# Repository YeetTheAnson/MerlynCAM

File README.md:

# MerlynCAM

https://github.com/user-attachments/assets/a9457055-48cb-43b0-b4a9-4c273cf0078e

https://github.com/user-attachments/assets/13ca98ed-bc15-4bd0-ae74-1581ccfe5670

## Introduction
This project was made possible thanks the reverse engineering efforts done by the OpenIPC team! You can check out their supported hardware here: https://openipc.org/supported-hardware/featured and the reference project here: https://oshwlab.com/oshwhub.com/openipc-vtx-ssc338q-30kq

This is my custom action camera, the MerlynCAM! This project was made to record HD footage on my FPV drones. It records video at 1080p@90, 1440p@60 and 4k@20. It also includes a BMI270 gyro to log motion data at 150Hz for Gyroflow video stabilization, and an ICS-43434 I2S microphone to capture propeller noise for the viewer's immersion.

The MerlynCAM is powered by the Sigmastar SSC338Q SOC. It is easy to use and includes a low power microcontroller onboard to manage the LED indicators, buttons, and power saving modes. There is only one button used for powering the camera on and off and starting and stopping recordings. The microcontroller handles the rest of the quality of life features in the background, such as battery level monitoring and auto power on when external voltage is detected in FPV mode. It also has an internal 1S battery with a BQ25606 charging circuit, so it can be used like a normal action cam or with the batteries removed to save weight on a drone.

## User Guide
The MerlynCAM is operated using a single button and it shows charge status and battery levels using a White LED

### Power & Recording Control
- **Power On:** Press the button once, then press and hold for 2 seconds. The White LED will blink rapidly while holding, then turn solid to indicate it is booting. Release the button afterwards.

> [!TIP]
> The camera will refuse to power on if the battery is below 5%

- **Power Off:** Press and hold the button for 4 seconds. The White LED will blink rapidly after 2 seconds, then blink twice and turn off.

- **Start/Stop Recording:** While the camera is powered on, hold the button for 1 second to start recording. Hold for 1 second again to stop recording.

### Battery Level Checking
While powered off, press the button once. The White LED will blink to indicate the current charge level:

- **\>95%:** 4 normal blinks + 3 rapid blinks

- **80-95%** 4 blinks

- **60-79%:** 3 blinks

- **40-59%:** 2 blinks

- **20-39%:** 1 blink

- **\< 5%:** 3 rapid blinks

### Passive Indicator
- **Charging:** The white LED will pulse slowly while charging. Once fully charged, it will remain solid until the power is disconnected

- **Battery Status:** The White LED automatically flashes the current battery percentage every 3.5 seconds

> [!IMPORTANT]
> Bridge the CHRG pad on the PCB if no battery is connected. This is necessary for the battery management IC to output a stable voltage on external power.

## Hardware Specifications
* **SOC:** Sigmastar SSC338Q
* **Camera Interface:** 30 pin mezzanine connector (compatible with Orange Pi 5)
* **IMU:** BMI270 @ I2C
* **Microphone:** ICS-43434 @ I2S
* **Storage:** Micro SD Card slot + W25Q128JVSIQ 16MB NOR Flash
* **Power Management & User Interface:** CH32V003F4U6
* **Battery Management:** BQ25606
* **Power Supply:** TPS63802 buck boost (3.3V), RT8097CHGE buck (1.0V and 1.5V), RT9193-18GB LDO (1.8V)

## Hardware Overview

> [!WARNING]
> When ordering from JLCPCB, make sure to enable impedance control and use the JLC04161H-3313 Stackup 

## Firmware
Because the SSC338Q is a proprietary chip, it must run the OpenIPC linux environment. Building the firmware requires a linux filesystem (Windows isn't supported)

> [!WARNING]
> At least 20GB of free space is required to build OpenIPC

### How to build the firmware (SSC338Q)
1. Clone the OpenIPC [firmware repository](https://github.com/openipc/firmware)
2. Run `make` and select the infinity6e architecture on the TUI.
3. Navigate to `output/build/linux-custom/arch/arm/boot/dts/` and replace `infinity6e-ssc012b-s01a.dts` with [infinity6e-ssc012b-s01a.dts](https://github.com/YeetTheAnson/MerlynCAM/blob/main/firmware/source/openIPC/infinity6e-ssc012b-s01a.dts).
4. Run `make linux-rebuild` to update the custom DTS changes into the kernel.
5. Navigate to `output/build/images` and extract `openipc.ssc338q-nand-ultimate.tgz` by entering `tar -xzf openipc.ssc338q-nand-ultimate.tgz`
6. Navigate to ssc338q-nand-ultimate and enter the command in your terminal
 `dd if=uImage.ssc338q of=openipc-ssc338q-nor-ultimate-16mb.bin bs=1K seek=384 conv=notrunc` and the binary file should appear

### How to build the firmware (CH32V003)
1. Clone [this repository](https://github.com/YeetTheAnson/MerlynCAM/tree/main) and enter the directory `cd MerlynCAM`
2. Open the `/firmware/source/powerManagement/powerManagement.ino` file in ArduinoIDE
3. Paste `https://alexandermandera.github.io/arduino-wch32v003/package_ch32v003_index.json` into File > Preferences > Additional boards manager URLs
4. Go to boards manager and install `WCH Boards` by Alexander Mandera
5. Click the upload button or Sketch > Export Compiled Binary

### How to flash the firmware (SSC338Q)
The W25Q128 16MB flash chip comes blank from the factory and the openIPC bootloader must be flashed before the operating system is able to boot.
1. Connect the CH341A USB programmer or a [makeshift Arduino programmer](https://controllerstech.com/arduino-w25q-flash-memory/) to flash the binary file to the W25Q128 flash chip. The file can be obtained in [firmware/binaries/(SSC338Q)openipc-nor-ultimate-16mb.bin](https://github.com/YeetTheAnson/MerlynCAM/blob/main/firmware/binaries/(SSC338Q)openipc-nor-ultimate-16mb.bin) or the [OpenIPC repository](https://openipc.org/cameras/vendors/sigmastar/socs/ssc338q/download_full_image?flash_size=16&flash_type=nor&fw_release=ultimate&layout=16) or compiled locally.

### How to flash the firmware (CH32V003)
1. Connect the WCH Link USB adapter to the SWDIO test point

2. Connect the USB C port. The MerlynCAM PCB and WCH Link USB adapter must share common ground (e.g. connected to the same laptop)
3. If compiling locally, press the upload button in Arduino IDE. Or use WCH-LinkUtility if flashing the pre compile binary in [powerManagement.bin](https://github.com/YeetTheAnson/MerlynCAM/blob/main/firmware/binaries/%28CH32V003%29powerManagement.bin)

## Assembly

### Component List
* **Shell:**
    - [case.stl](https://github.com/YeetTheAnson/MerlynCAM/blob/main/production/3dPrint/case.stl)
    - [lid.stl](https://github.com/YeetTheAnson/MerlynCAM/blob/main/production/3dPrint/lid.stl)
    - [button.stl](https://github.com/YeetTheAnson/MerlynCAM/blob/main/production/3dPrint/button.stl)
* **PCB:**
    - [MerlynCAM.zip](https://github.com/YeetTheAnson/MerlynCAM/blob/main/production/PCB/MerlynCAM.zip)
* **Camera:** IMX415 camera module for Orange Pi 5 + 30P MIPI cable
* **Fasteners:**
    - 8x M2 6mm Self Tapping Screws
    - 4x M2 4mm Self Tapping Screws
* **Battery:** Generic 500mAh LiPo battery
* **SD Card:** Generic micro SD Card

### Assembly Instructions

1. Place IMX415 camera module in the case and secure with 4x 6mm Self Tapping Screws.

2. Insert button with the hole side facing up.

3. Solder the battery wires to designated pads and place the battery and PCB into the case. Route the MIPI cable through the recess of the case wall and connect to the mezzanine connector.

4. Secure the PCB to the case with 4x 6mm Self Tapping Screws.

5. Put on the case lid and secure with 4x 4mm Self Tapping Screws.

## Bill of Material
Note: The prices in USD are converted as of 1 September 2026 and may fluctuate. The costs of separate components are cheaper than JLCPCB assembly.

| Category | Item Name | Description | Link | Vendor | Quantity | Total Price (USD) |
|---|---|---|---|---|---:|---:|
| PCB Components | CL10A106MA8NRNC | 10uF 0603 capacitor | [link](https://www.lcsc.com/product-detail/C96446.html) | LCSC | 20 | 1.30 |
| PCB Components | CL05A475MP5NRNC | 4.7uF 0402 capacitor | [link](https://www.lcsc.com/product-detail/C23733.html) | LCSC | 50 | 1.17 |
| PCB Components | CL05B104KB54PNC | 0.1uF 0402 capacitor | [link](https://www.lcsc.com/product-detail/C307331.html) | LCSC | 100 | 0.89 |
| PCB Components | CC0402KRX7R9BB473 | 47nF 0402 capacitor | [link](https://www.lcsc.com/product-detail/C272875.html) | LCSC | 100 | 0.41 |
| PCB Components | CL05A105KA5NQNC | 1uF 0402 capacitor | [link](https://www.lcsc.com/product-detail/C52923.html) | LCSC | 50 | 0.61 |
| PCB Components | CL10A226MQ8NRNC | 22uF 0603 capacitor | [link](https://www.lcsc.com/product-detail/C59461.html) | LCSC | 20 | 0.63 |
| PCB Components | 0402B223K500NT | 22nF 0402 capacitor | [link](https://www.lcsc.com/product-detail/C1532.html) | LCSC | 50 | 0.58 |
| PCB Components | 0402CG8R0C500NT | 8pF 0402 capacitor | [link](https://www.lcsc.com/product-detail/C1578.html) | LCSC | 100 | 0.36 |
| PCB Components | CDZVT2R5.1B | 5.1V Clamp SOD923 zener | [link](https://www.lcsc.com/product-detail/C414245.html) | LCSC | 20 | 0.64 |
| PCB Components | HC-1.0-4PWT | 4P JST-SH connector | [link](https://www.lcsc.com/product-detail/C2845363.html) | LCSC | 5 | 0.47 |
| PCB Components | FTC201610S1R5MBCA | 1.5uH 0806 inductor | [link](https://www.lcsc.com/product-detail/C5832343.html) | LCSC | 10 | 0.98 |
| PCB Components | FTC201610SR47MBCA | 0.47 uH 0806 inductor | [link](https://www.lcsc.com/product-detail/C5832340.html) | LCSC | 10 | 0.98 |
| PCB Components | YLED0602RSIDE | Red 0602 right angle LED | [link](https://www.lcsc.com/product-detail/C49446796.html) | LCSC | 20 | 0.49 |
| PCB Components | YLED0602WSIDE | White 0602 right angle LED | [link](https://www.lcsc.com/product-detail/C46635136.html) | LCSC | 50 | 0.99 |
| PCB Components | AO3401A | P channel MOSFET | [link](https://www.lcsc.com/product-detail/C15127.html) | LCSC | 5 | 0.49 |
| PCB Components | 0402WGF1003TCE | 100k 0402 resistor | [link](https://www.lcsc.com/product-detail/C25741.html) | LCSC | 100 | 0.28 |
| PCB Components | FRC0402F2700TS | 270R 0402 resistor | [link](https://www.lcsc.com/product-detail/C2909342.html) | LCSC | 100 | 0.25 |
| PCB Components | FRC0402F9100TS | 910R 0402 resistor | [link](https://www.lcsc.com/product-detail/C2909392.html) | LCSC | 100 | 0.18 |
| PCB Components | 0402WGF1002TCE | 10k 0402 resistor | [link](https://www.lcsc.com/product-detail/C25744.html) | LCSC | 100 | 0.31 |
| PCB Components | 0402WGF5101TCE | 5.1k 0402 resistor | [link](https://www.lcsc.com/product-detail/C25905.html) | LCSC | 100 | 0.26 |
| PCB Components | 0402WGF5602TCE | 56k 0402 resistor | [link](https://www.lcsc.com/product-detail/C25796.html) | LCSC | 100 | 0.68 |
| PCB Components | 0402WGF1502TCE | 15k 0402 resistor | [link](https://www.lcsc.com/product-detail/C25756.html) | LCSC | 100 | 0.58 |
| PCB Components | FRC0402F3602TS | 36k 0402 resistor | [link](https://www.lcsc.com/product-detail/C2930004.html) | LCSC | 100 | 0.19 |
| PCB Components | 0402WGF1000TCE | 100R 0402 resistor | [link](https://www.lcsc.com/product-detail/C25076.html) | LCSC | 100 | 0.77 |
| PCB Components | 0402WGF5102TCE | 51k 0402 resistor | [link](https://www.lcsc.com/product-detail/C25794.html) | LCSC | 100 | 0.19 |
| PCB Components | 0402WGF4701TCE | 4.7k 0402 resistor | [link](https://www.lcsc.com/product-detail/C25900.html) | LCSC | 100 | 0.29 |
| PCB Components | 0402WGF2003TCE | 200k 0402 resistor | [link](https://www.lcsc.com/product-detail/C25764.html) | LCSC | 100 | 0.32 |
| PCB Components | TS24CA | Right angle button | [link](https://www.lcsc.com/product-detail/C393942.html) | LCSC | 20 | 0.51 |
| PCB Components | TPS63802DLAR | Buck boost converter | [link](https://www.lcsc.com/product-detail/C2845237.html) | LCSC | 2 | 2.05 |
| PCB Components | BQ25606RGER | Battery charge and management | [link](https://www.lcsc.com/product-detail/C374063.html) | LCSC | 1 | 1.63 |
| PCB Components | RT8097CHGE | Buck converter | [link](https://www.lcsc.com/product-detail/C3031673.html) | LCSC | 5 | 0.80 |
| PCB Components | CH32V003F4U6 | CH32 for interface and power management | [link](https://www.lcsc.com/product-detail/C5299908.html) | LCSC | 5 | 1.58 |
| PCB Components | RT9193-18GB | 1.8V Linear LDO regulator | [link](https://www.lcsc.com/product-detail/C27416.html) | LCSC | 5 | 0.83 |
| PCB Components | ICS-43434 | I2S MEMS microphone | [link](https://www.lcsc.com/product-detail/C5656610.html) | LCSC | 1 | 4.13 |
| PCB Components | BMI270 | IMU | [link](https://www.lcsc.com/product-detail/C2836813.html) | LCSC | 1 | 3.25 |
| PCB Components | W25Q128JVSIQ | 16 MB NOR flash | [link](https://www.lcsc.com/product-detail/C97521.html) | LCSC | 1 | 2.62 |
| PCB Components | TF-115-BCP9 | SD card connector | [link](https://www.lcsc.com/product-detail/C720505.html) | LCSC | 5 | 0.49 |
| PCB Components | TYPE-C 16PIN 2MD(073) | TYPE C Connector | [link](https://www.lcsc.com/product-detail/C2765186.html) | LCSC | 20 | 1.49 |
| PCB Components | T201624MBBCE2X | 24MHz 2016 crystal resonator | [link](https://www.lcsc.com/product-detail/C7303340.html) | LCSC | 10 | 0.71 |
| PCB Components | LCSC Shipping | 4PX | - | 4PX | 1 | 5.48 |
| PCB | PCB | Bare PCB | - | JLCPCB | 1 | 2.00 |
| PCB | Stencil | Stencil | - | JLCPCB | 1 | 6.36 |
| PCB | JLCPCB Shipping | Shipping | - | E-POST | 1 | 6.68 |
| Parts | OK-10F030-04 | 30P 0.4mm Mezzanine connector | [link](https://www.aliexpress.com/item/1005008289234567.html) | AliExpress | 1 | 2.09 |
| Parts | SSC338Q | Main recording SOC | [link](https://www.aliexpress.com/item/1005009947110808.html) | AliExpress | 1 | 16.99 |
| Parts | IMX415 camera module | IMX415 camera module 140 FOV | [link](https://www.aliexpress.com/item/1005009005078802.html) | AliExpress | 1 | 32.69 |
| Parts | AliExpress Shipping | Shipping | - | AliExpress | 1 | 9.74 |

### **Grand Total:** \$117.41

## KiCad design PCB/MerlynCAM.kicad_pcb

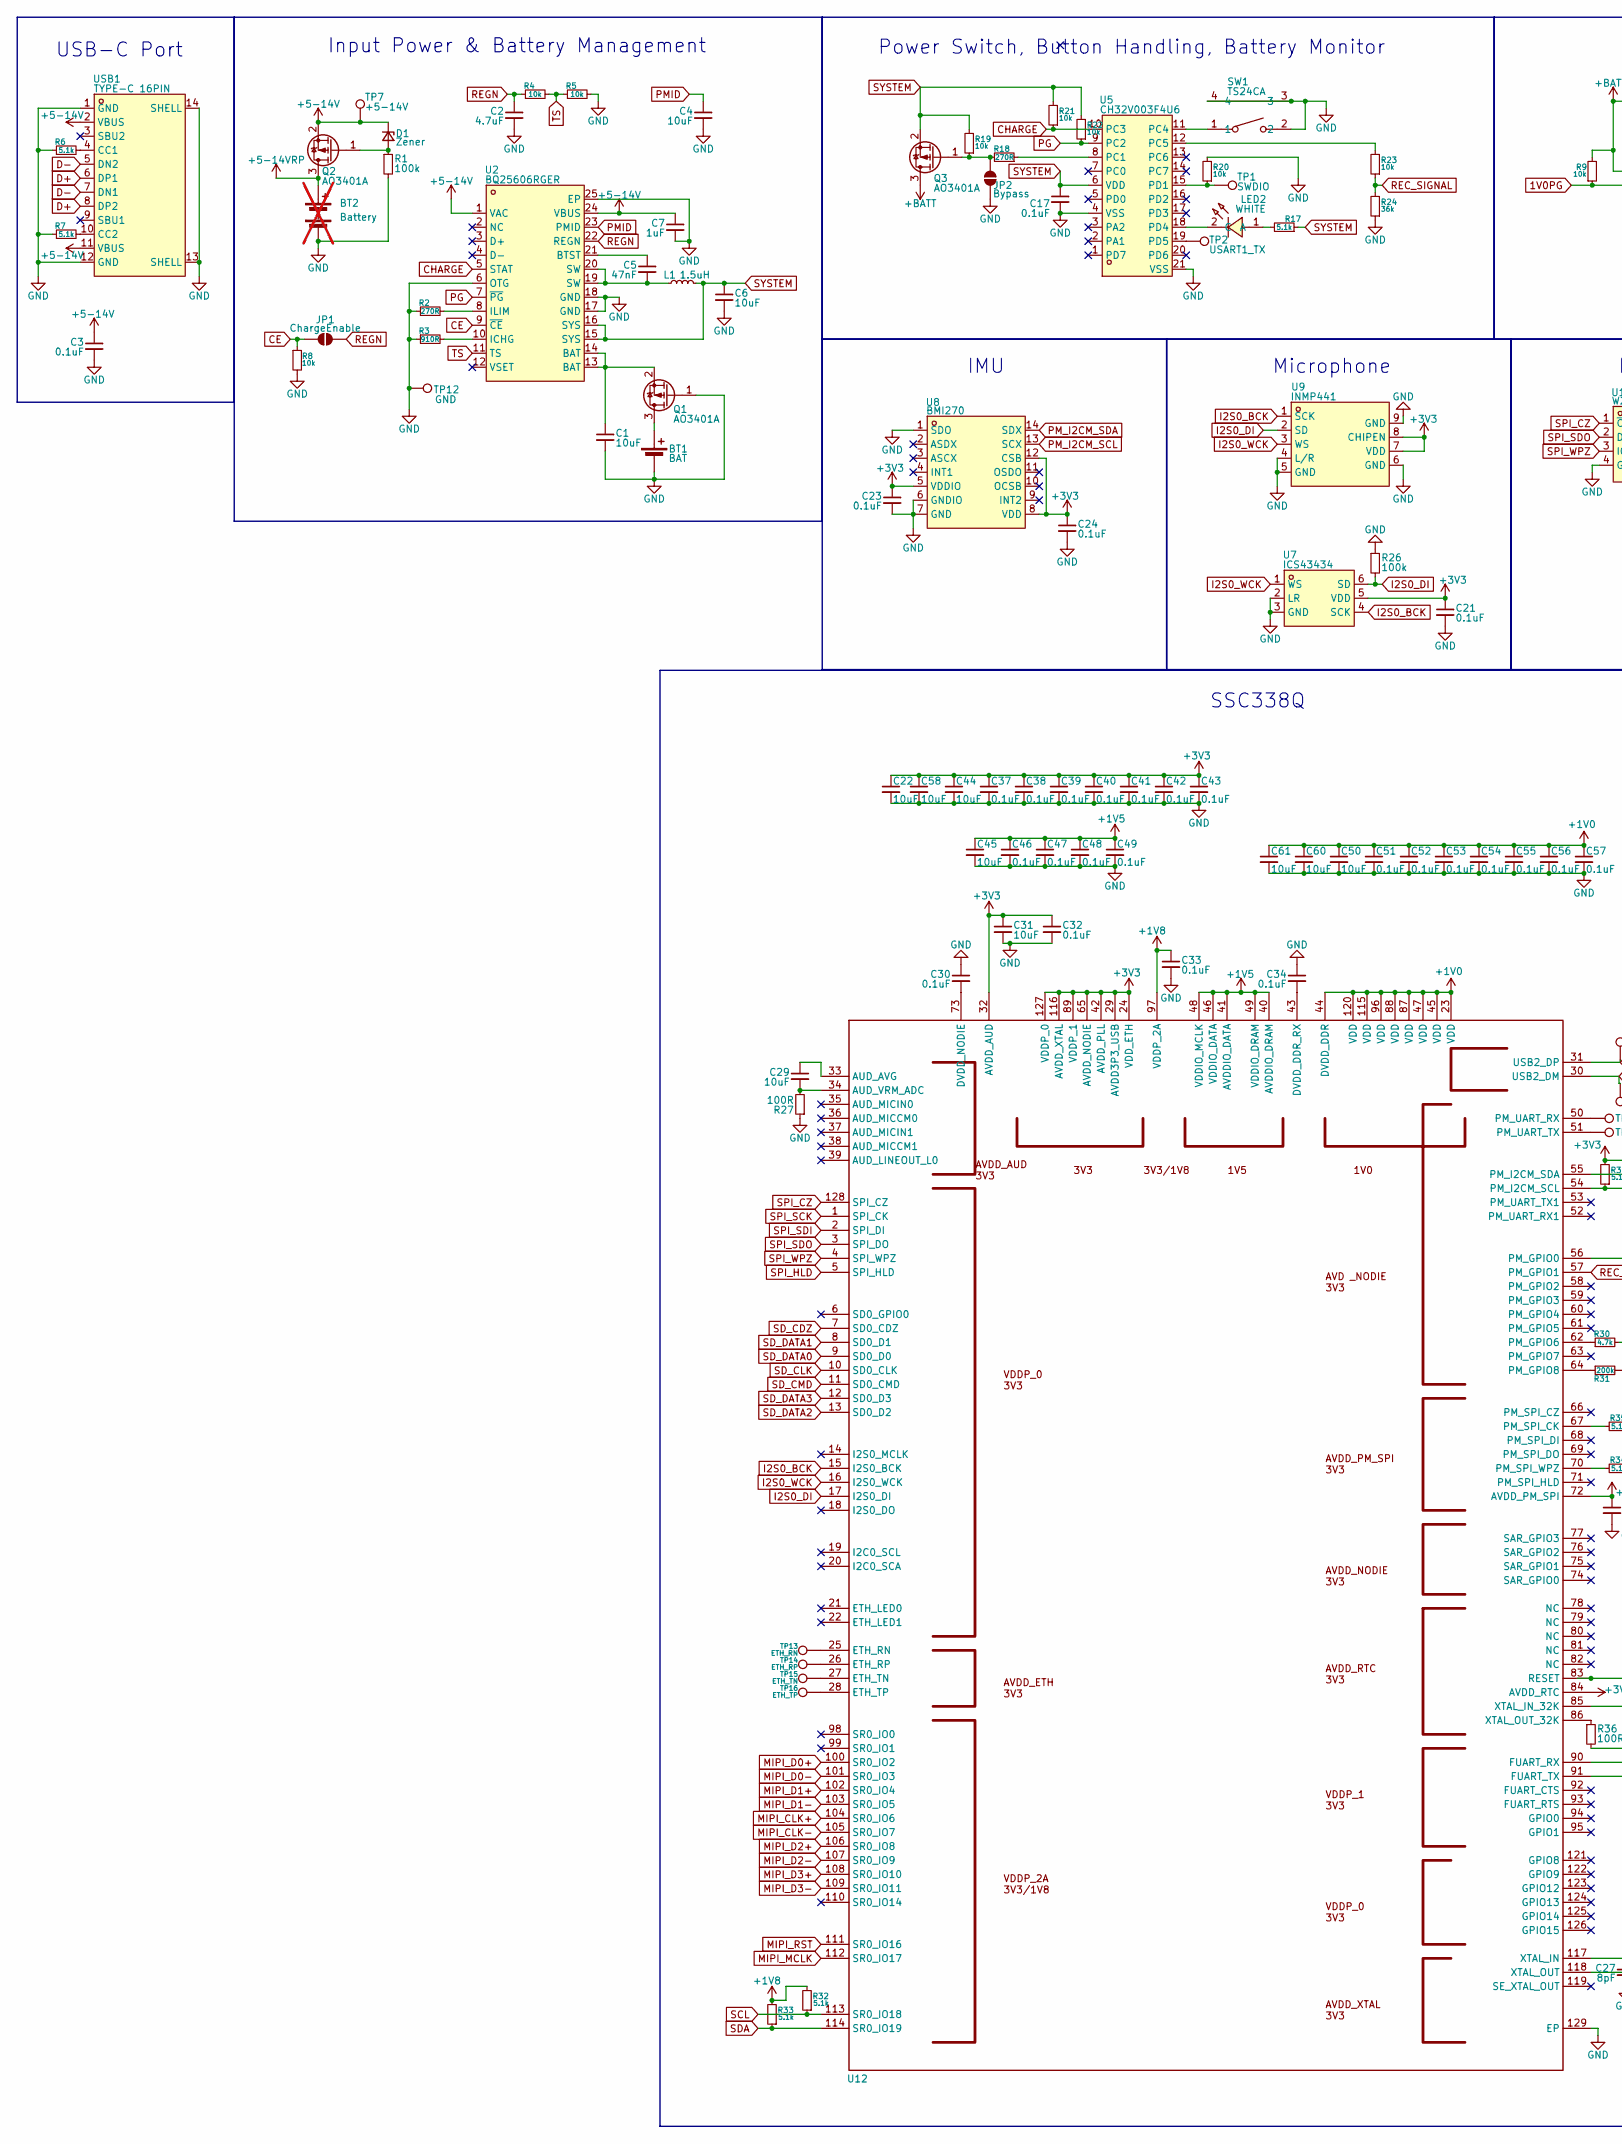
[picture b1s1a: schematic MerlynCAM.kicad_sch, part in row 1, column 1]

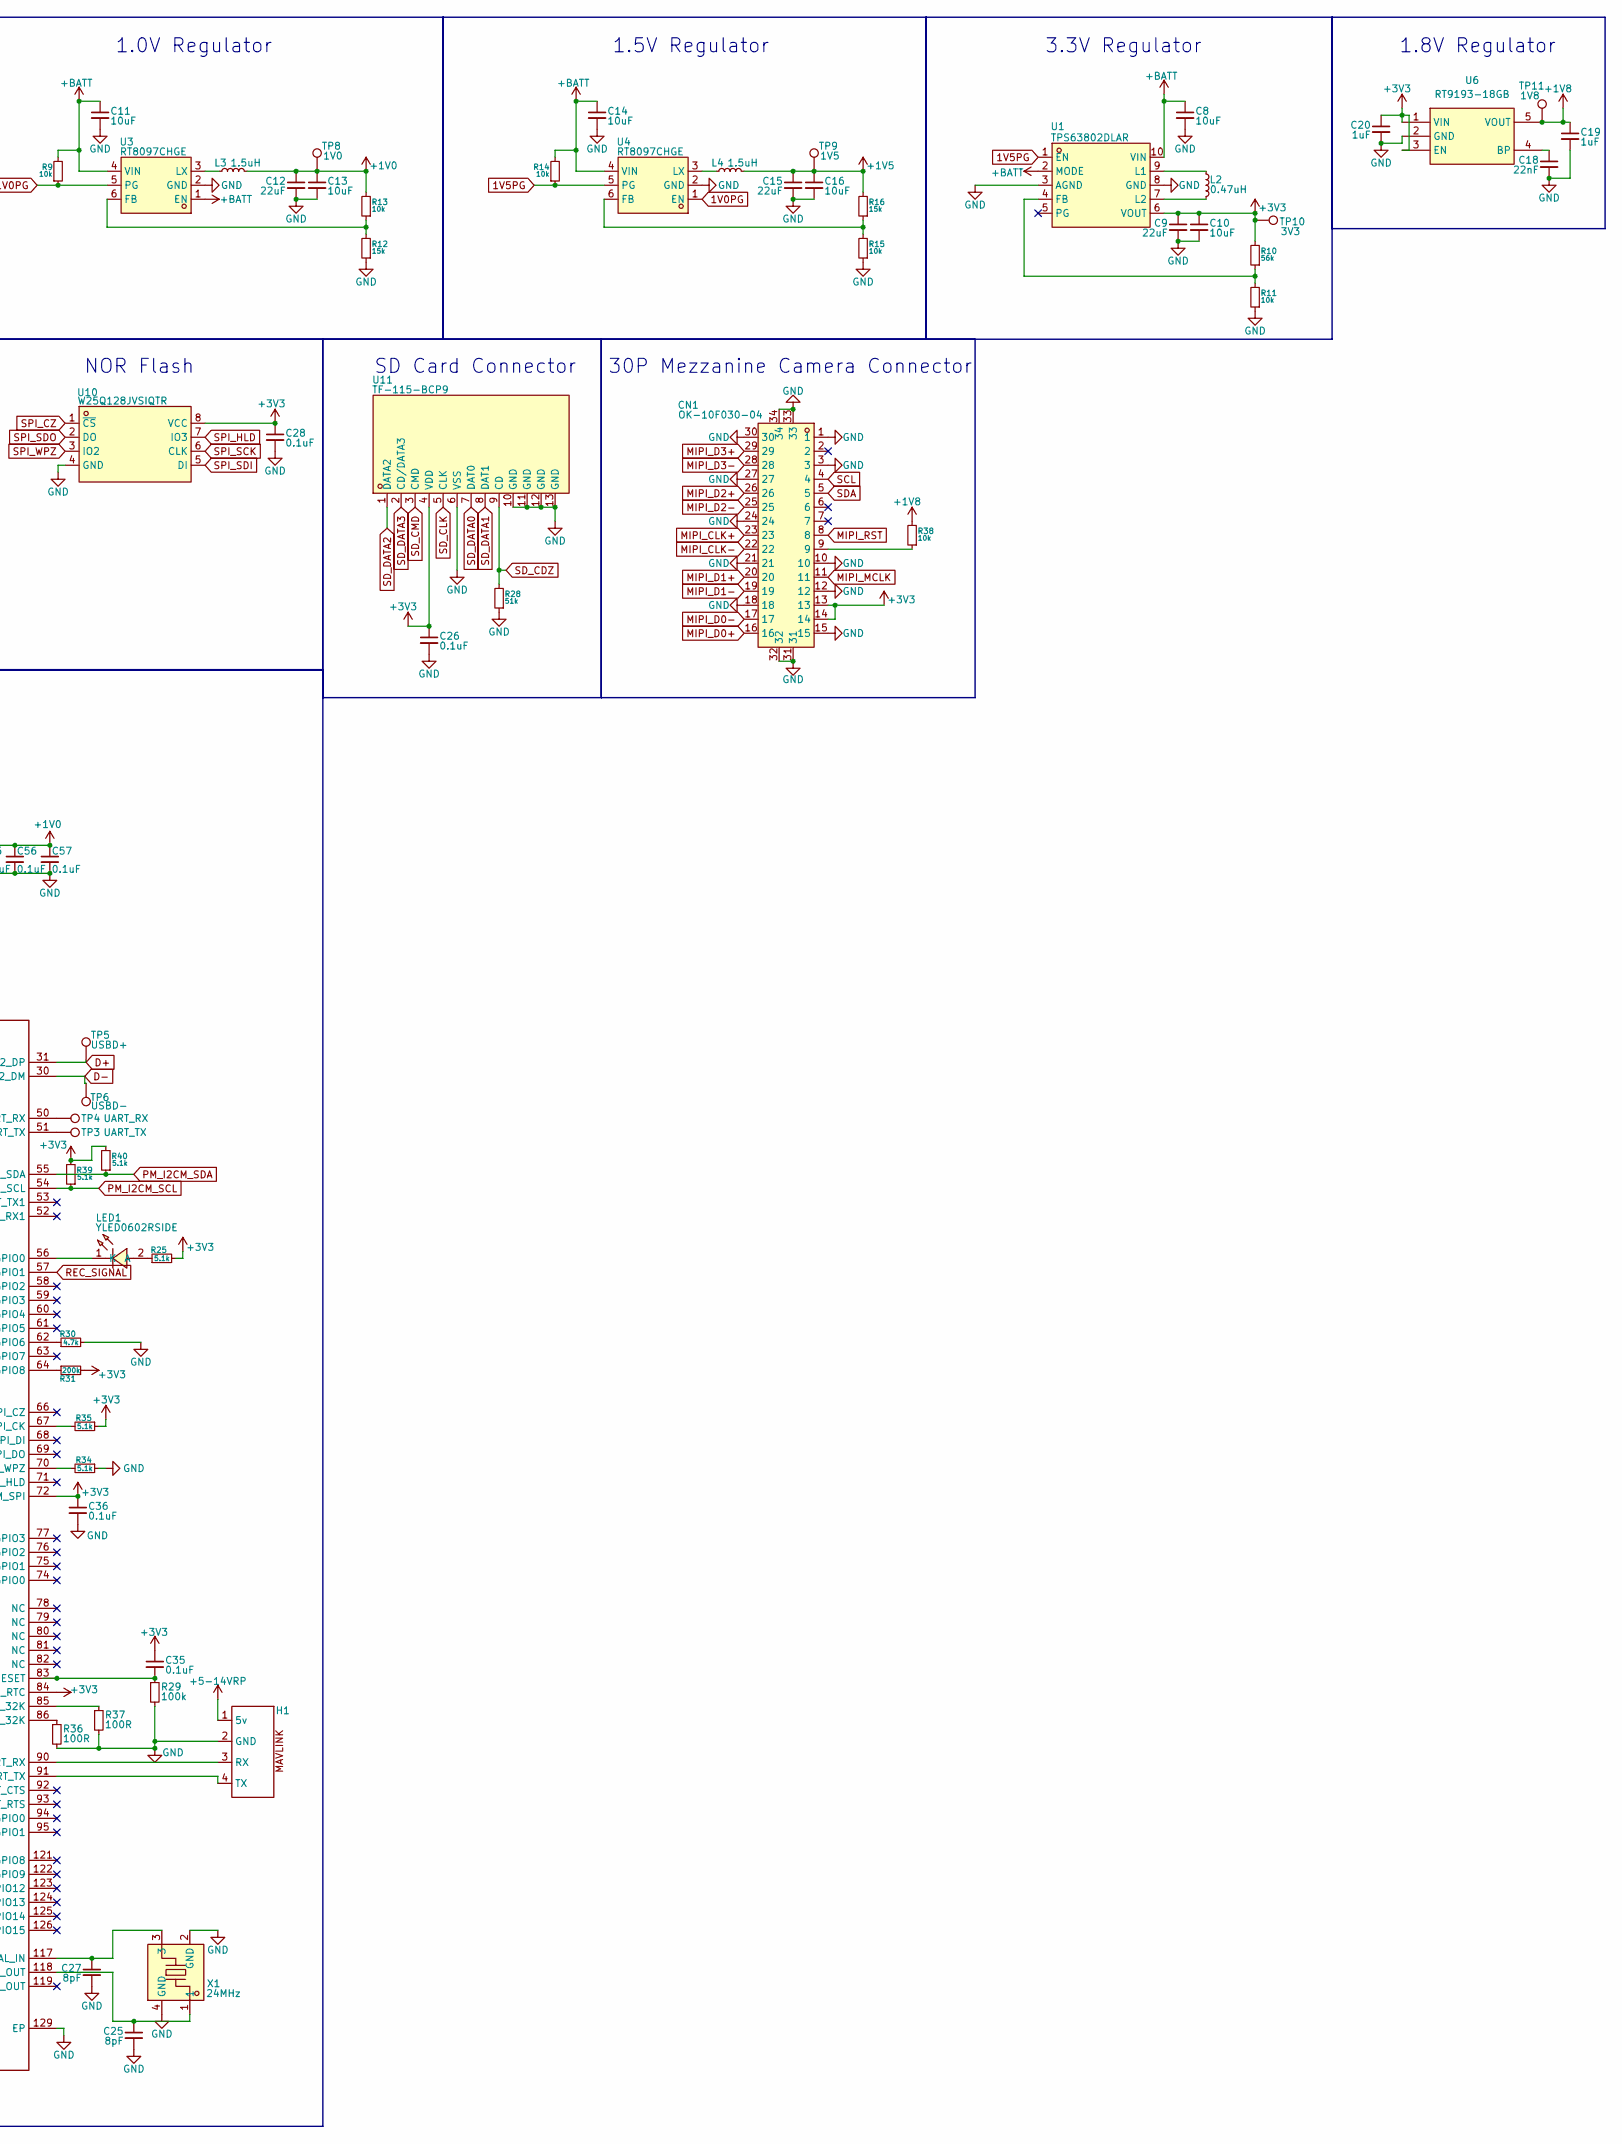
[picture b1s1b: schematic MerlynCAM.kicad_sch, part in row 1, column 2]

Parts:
BT1: BAT; Battery
BT2: Battery; not fitted
C1, C4, C6, C8, C10, C11, C13, C14, C16, C22, C29, C31, C44, C45, C50, C58, C60, C61: 10uF; C_0603_1608Metric; LCSC Part C96446
C2: 4.7uF; C_0402_1005Metric; LCSC Part C23733
C3, C17, C21, C23, C24, C26, C28, C30, C32, C33, C34, C35, C36, C37, C38, C39, C40, C41, C42, C43, C46, C47, C48, C49, C51, C52, C53, C54, C55, C56, C57: 0.1uF; C_0402_1005Metric; LCSC Part C307331
C5: 47nF; C_0402_1005Metric; LCSC Part C272875
C7, C19, C20: 1uF; C_0402_1005Metric; LCSC Part C52923
C9, C12, C15: 22uF; C_0603_1608Metric; LCSC Part C59461
C18: 22nF; C_0402_1005Metric; LCSC Part C1532
C25, C27: 8pF; C_0402_1005Metric; LCSC Part C1578
CN1: OK-10F030-04; CONN-SMD_30P-P0.40_OK-10F030-04-A; MPN OK-10F030-04; LCSC Part C9900021743
D1: Zener; D_SOD-923; LCSC Part C414245
H1: JST_SH_SM04B-SRSS-TB_1x04-1MP_P1.00mm_Horizontal; LCSC Part C2845363
JP1: ChargeEnable; SolderJumper-2_P1.3mm_Open_TrianglePad1.0x1.5mm
JP2: Bypass; SolderJumper-2_P1.3mm_Open_TrianglePad1.0x1.5mm
L1, L3, L4: 1.5uH; L_Changjiang_FTC201610S; LCSC Part C5832343
L2: 0.47uH; L_Changjiang_FTC201610S; LCSC Part C5832340
LED1: YLED0602RSIDE; LED-SMD_L1.6-W1.1-RD; MPN YLED0602RSIDE; LCSC Part C49446796
LED2: WHITE; LED-SMD_L1.6-W1.1-R-RD_WHITE; MPN YLED0602WSIDE; LCSC Part C46635136
Q1, Q2, Q3: AO3401A; SOT-23; LCSC Part C15127
R1, R26, R29: 100k; R_0402_1005Metric; LCSC Part C25741
R2, R18: 270R; R_0402_1005Metric; LCSC Part C2909342
R3: 910R; R_0402_1005Metric; LCSC Part C2909392
R4, R5, R8, R9, R11, R13, R14, R15, R19, R20, R21, R22, R23, R38: 10k; R_0402_1005Metric; LCSC Part C25744
R6, R7, R17, R25, R32, R33, R34, R35, R39, R40: 5.1k; R_0402_1005Metric; LCSC Part C25905
R10: 56k; R_0402_1005Metric; LCSC Part C25796
R12, R16: 15k; R_0402_1005Metric; LCSC Part C25756
R24: 36k; R_0402_1005Metric; LCSC Part C2930004
R27, R36, R37: 100R; R_0402_1005Metric; LCSC Part C25076
R28: 51k; R_0402_1005Metric; LCSC Part C25794
R30: 4.7k; R_0402_1005Metric; LCSC Part C25900
R31: 200k; R_0402_1005Metric; LCSC Part C25764
SW1: TS24CA; SW-SMD_2P-TS24CA; MPN TS24CA; LCSC Part C393942
TP1: SWDIO; TestPoint
TP2: USART1_TX; TestPoint
TP3: UART_TX; TestPoint
TP4: UART_RX; TestPoint
TP5: USBD+; TestPoint
TP6: USBD-; TestPoint
TP7: +5-14V; TestPoint
TP8: 1V0; TestPoint
TP9: 1V5; TestPoint
TP10: 3V3; TestPoint
TP11: 1V8; TestPoint
TP12: GND; TestPoint
TP13: ETH_RN; TestPoint
TP14: ETH_RP; TestPoint
TP15: ETH_TN; TestPoint
TP16: ETH_TP; TestPoint
U1: TPS63802DLAR; VSON-10_L3.0-W2.0-P0.50-TL; MPN TPS63802DLAR; LCSC Part C2845237
U2: BQ25606RGER; VQFN-24_L4.0-W4.0-P0.50-TL-EP2.8; MPN BQ25606RGER; LCSC Part C374063
U3, U4: RT8097CHGE; SOT-23-6_L2.9-W1.6-P0.95-LS2.8-BL; MPN RT8097CHGE; LCSC Part C3031673
U5: CH32V003F4U6; QFN-20_L3.0-W3.0-P0.40-TL-EP1.7; MPN CH32V003F4U6; LCSC Part C5299908
U6: RT9193-18GB; SOT-23-5_L3.0-W1.7-P0.95-LS2.8-BR; MPN RT9193-18GB; LCSC Part C27416
U7: ICS43434; MIC-SMD_6P-L3.5-W2.7-P0.90-BL; MPN ICS-43434; LCSC Part C5656610
U8: BMI270; LGA-14_L3.0-W2.5-P0.50-BR; MPN BMI270; LCSC Part C2836813
U9: INMP441; MIC-SMD_INMP441; MPN INMP441; LCSC Part C5438445
U10: W25Q128JVSIQTR; SOIC-8_L5.3-W5.3-P1.27-LS8.0-BL; MPN W25Q128JVSIQ; LCSC Part C97521
U11: TF-115-BCP9; TF-SMD_TF-115-BCP9; MPN TF-115-BCP9; LCSC Part C720505
U12: QFN128_12.3_12.3
USB1: TYPE-C 16PIN; USB-C-SMD_TYPE-C-6PIN-2MD-073; LCSC Part C2765186
X1: 24MHz; CRYSTAL-SMD_4P-L2.0-W1.6-BL; MPN T201624MBBCE2X; LCSC Part C7303340

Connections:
1V0PG: R9.1, U3.5 (PG), U4.1 (EN)
1V5PG: R14.1, U1.1 (EN), U4.5 (PG)
+1V0: C12.1, C13.1, C50.1, C51.1, C52.1, C53.1, C54.1, C55.1, C56.1, C57.1, C60.1, C61.1, L3.2, R13.2, TP8.1, U12.23 (VDD), U12.44 (DVDD_DDR), U12.45 (VDD), U12.47 (VDD), U12.87 (VDD), U12.88 (VDD), U12.96 (VDD), U12.115 (VDD), U12.120 (VDD)
+1V5: C15.1, C16.1, C45.1, C46.1, C47.1, C48.1, C49.1, L4.2, R16.2, TP9.1, U12.40 (AVDDIO_DRAM), U12.41 (AVDDIO_DATA), U12.46 (VDDIO_DATA), U12.48 (VDDIO_MCLK), U12.49 (VDDIO_DRAM)
+1V8: C19.1, C33.1, R32.2, R33.2, R38.2, TP11.1, U6.5 (VOUT), U12.97 (VDDP_2A)
+3V3: C9.1, C10.1, C20.1, C21.1, C22.1, C23.1, C24.1, C26.1, C28.1, C31.1, C32.1, C35.1, C36.1, C37.1, C38.1, C39.1, C40.1, C41.1, C42.1, C43.1, C44.1, C58.1, CN1.13, CN1.14, R10.2, R25.2, R31.2, R35.1, R39.2, R40.2, TP10.1, U1.6 (VOUT), U6.1 (VIN), U6.3 (EN), U7.5 (VDD), U8.5 (VDDIO), U8.8 (VDD), U8.12 (CSB), U9.7 (VDD), U9.8 (CHIPEN), U10.8 (VCC), U11.4 (VDD), U12.24 (VDD_ETH), U12.29 (AVDD3P3_USB), U12.32 (AVDD_AUD), U12.42 (AVDD_PLL), U12.65 (AVDD_NODIE), U12.72 (AVDD_PM_SPI), U12.84 (AVDD_RTC), U12.89 (VDDP_1), U12.116 (AVDD_XTAL), U12.127 (VDDP_0)
+5-14V: C3.1, C7.1, D1.1 (K), Q2.2 (S), TP7.1, U2.1 (VAC), U2.24 (VBUS), USB1.2 (VBUS), USB1.11 (VBUS)
+5-14VRP: BT2.1 (+), H1.1 (5v), Q2.3 (D)
+BATT: C8.1, C11.1, C14.1, Q3.3 (D), R9.2, R14.2, U1.2 (MODE), U1.10 (VIN), U3.1 (EN), U3.4 (VIN), U4.4 (VIN)
CE: JP1.1 (A), R8.1, U2.9 (~CE)
CHARGE: R21.1, U2.5 (STAT), U5.10 (PC3)
D+: TP5.1, U12.31 (USB2_DP), USB1.6 (DP1), USB1.8 (DP2)
D-: TP6.1, U12.30 (USB2_DM), USB1.5 (DN2), USB1.7 (DN1)
GND: BT1.2 (-), BT2.2 (-), C1.2, C2.2, C3.2, C4.2, C6.2, C7.2, C8.2, C9.2, C10.2, C11.2, C12.2, C13.2, C14.2, C15.2, C16.2, C17.2, C18.2, C19.2, C20.2, C21.2, C22.2, C23.2, C24.2, C25.2, C26.2, C27.2, C28.2, C30.1, C31.2, C32.2, C33.2, C34.1, C36.2, C37.2, C38.2, C39.2, C40.2, C41.2, C42.2, C43.2, C44.2, C45.2, C46.2, C47.2, C48.2, C49.2, C50.2, C51.2, C52.2, C53.2, C54.2, C55.2, C56.2, C57.2, C58.2, C60.2, C61.2, CN1.1, CN1.3, CN1.10, CN1.12, CN1.15, CN1.18, CN1.21, CN1.24, CN1.27, CN1.30, CN1.31, CN1.32, CN1.33, CN1.34, H1.2 (GND), JP2.1 (A), Q1.1 (G), R1.2, R2.1, R3.1, R5.2, R6.1, R7.1, R8.2, R11.1, R12.1, R15.1, R20.2, R24.1, R26.1, R27.1, R28.1, R29.2, R30.2, R34.1, R36.2, R37.2, SW1.2, SW1.3, SW1.4, TP12.1, U1.3 (AGND), U1.8 (GND), U2.6 (OTG), U2.17 (GND), U2.18 (GND), U2.25 (EP), U3.2 (GND), U4.2 (GND), U5.4 (VSS), U5.21 (VSS), U6.2 (GND), U7.2 (LR), U7.3 (GND), U8.1 (SDO), U8.6 (GNDIO), U8.7 (GND), U9.4 (L/R), U9.5 (GND), U9.6 (GND), U9.9 (GND), U10.4 (GND), U11.6 (VSS), U11.10 (GND), U11.11 (GND), U11.12 (GND), U11.13 (GND), U12.129 (EP), USB1.1 (GND), USB1.12 (GND), USB1.13 (SHELL), USB1.14 (SHELL), X1.2 (GND), X1.4 (GND)
I2S0_BCK: U7.4 (SCK), U9.1 (SCK), U12.15 (I2S0_BCK)
I2S0_DI: R26.2, U7.6 (SD), U9.2 (SD), U12.17 (I2S0_DI)
I2S0_WCK: U7.1 (WS), U9.3 (WS), U12.16 (I2S0_WCK)
MIPI_CLK+: CN1.23, U12.104 (SR0_IO6)
MIPI_CLK-: CN1.22, U12.105 (SR0_IO7)
MIPI_D0+: CN1.16, U12.100 (SR0_IO2)
MIPI_D0-: CN1.17, U12.101 (SR0_IO3)
MIPI_D1+: CN1.20, U12.102 (SR0_IO4)
MIPI_D1-: CN1.19, U12.103 (SR0_IO5)
MIPI_D2+: CN1.26, U12.106 (SR0_IO8)
MIPI_D2-: CN1.25, U12.107 (SR0_IO9)
MIPI_D3+: CN1.29, U12.108 (SR0_IO10)
MIPI_D3-: CN1.28, U12.109 (SR0_IO11)
MIPI_MCLK: CN1.11, U12.112 (SR0_IO17)
MIPI_RST: CN1.8, U12.111 (SR0_IO16)
unnamed: BT1.1 (+), Q1.3 (D)
unnamed: C5.2, L1.1, U2.19 (SW), U2.20 (SW)
unnamed: CN1.9, R38.1
unnamed: D1.2 (A), Q2.1 (G), R1.1
unnamed: H1.3 (RX), U12.90 (FUART_RX)
unnamed: H1.4 (TX), U12.91 (FUART_TX)
unnamed: JP2.2 (B), Q3.1 (G), R18.2, R19.1
unnamed: LED1.2 (A), R25.1
unnamed: LED1.1 (K), U12.56 (PM_GPIO0)
unnamed: LED2.1 (A), R17.2
unnamed: LED2.2 (C), U5.18 (PD4)
unnamed: C1.1, Q1.2 (S), U2.13 (BAT), U2.14 (BAT)
unnamed: R10.1, R11.2, U1.4 (FB)
unnamed: L2.1, U1.9 (L1)
unnamed: L2.2, U1.7 (L2)
unnamed: C5.1, U2.21 (BTST)
unnamed: R3.2, U2.10 (ICHG)
unnamed: R2.2, U2.8 (ILIM)
unnamed: R12.2, R13.1, U3.6 (FB)
unnamed: L3.1, U3.3 (LX)
unnamed: R15.2, R16.1, U4.6 (FB)
unnamed: L4.1, U4.3 (LX)
unnamed: R18.1, U5.8 (PC1)
unnamed: SW1.1, U5.11 (PC4)
unnamed: R23.2, U5.12 (PC5)
unnamed: R20.1, TP1.1, U5.15 (PD1)
unnamed: TP2.1, U5.19 (PD5)
unnamed: C18.1, U6.4 (BP)
unnamed: C29.1, U12.33 (AUD_AVG)
unnamed: C29.2, R27.2, U12.34 (AUD_VRM_ADC)
unnamed: C34.2, U12.43 (DVDD_DDR_RX)
unnamed: C30.2, U12.73 (DVDD_NODIE)
unnamed: TP13.1, U12.25 (ETH_RN)
unnamed: TP14.1, U12.26 (ETH_RP)
unnamed: TP15.1, U12.27 (ETH_TN)
unnamed: TP16.1, U12.28 (ETH_TP)
unnamed: R30.1, U12.62 (PM_GPIO6)
unnamed: R31.1, U12.64 (PM_GPIO8)
unnamed: R35.2, U12.67 (PM_SPI_CK)
unnamed: R34.2, U12.70 (PM_SPI_WPZ)
unnamed: TP4.1, U12.50 (PM_UART_RX)
unnamed: TP3.1, U12.51 (PM_UART_TX)
unnamed: C35.2, R29.1, U12.83 (RESET)
unnamed: C27.1, U12.117 (XTAL_IN), X1.3
unnamed: R37.1, U12.85 (XTAL_IN_32K)
unnamed: C25.1, U12.118 (XTAL_OUT), X1.1
unnamed: R36.1, U12.86 (XTAL_OUT_32K)
unnamed: R6.2, USB1.4 (CC1)
unnamed: R7.2, USB1.10 (CC2)
PG: R22.1, U2.7 (~PG), U5.9 (PC2)
PMID: C4.1, U2.23 (PMID)
PM_I2CM_SCL: R39.1, U8.13 (SCX), U12.54 (PM_I2CM_SCL)
PM_I2CM_SDA: R40.1, U8.14 (SDX), U12.55 (PM_I2CM_SDA)
REC_SIGNAL: R23.1, R24.2, U12.57 (PM_GPIO1)
REGN: C2.1, JP1.2 (B), R4.1, U2.22 (REGN)
SCL: CN1.4, R32.1, U12.113 (SR0_IO18)
SDA: CN1.5, R33.1, U12.114 (SR0_IO19)
SD_CDZ: R28.2, U11.9 (CD), U12.7 (SD0_CDZ)
SD_CLK: U11.5 (CLK), U12.10 (SD0_CLK)
SD_CMD: U11.3 (CMD), U12.11 (SD0_CMD)
SD_DATA0: U11.7 (DAT0), U12.9 (SD0_D0)
SD_DATA1: U11.8 (DAT1), U12.8 (SD0_D1)
SD_DATA2: U11.1 (DATA2), U12.13 (SD0_D2)
SD_DATA3: U11.2 (CD/DATA3), U12.12 (SD0_D3)
SPI_CZ: U10.1 (~CS), U12.128 (SPI_CZ)
SPI_HLD: U10.7 (IO3), U12.5 (SPI_HLD)
SPI_SCK: U10.6 (CLK), U12.1 (SPI_CK)
SPI_SDI: U10.5 (DI), U12.2 (SPI_DI)
SPI_SDO: U10.2 (DO), U12.3 (SPI_DO)
SPI_WPZ: U10.3 (IO2), U12.4 (SPI_WPZ)
SYSTEM: C6.1, C17.1, L1.2, Q3.2 (S), R17.1, R19.2, R21.2, R22.2, U2.15 (SYS), U2.16 (SYS), U5.6 (VDD)
TS: R4.2, R5.1, U2.11 (TS)

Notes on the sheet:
30P Mezzanine Camera Connector
USB-C Port
1.5V Regulator
3.3V Regulator
Power Switch, Button Handling, Battery Monitor
1.8V Regulator
Input Power & Battery Management
NOR Flash
Microphone
SSC338Q
SD Card Connector
1.0V Regulator
IMU

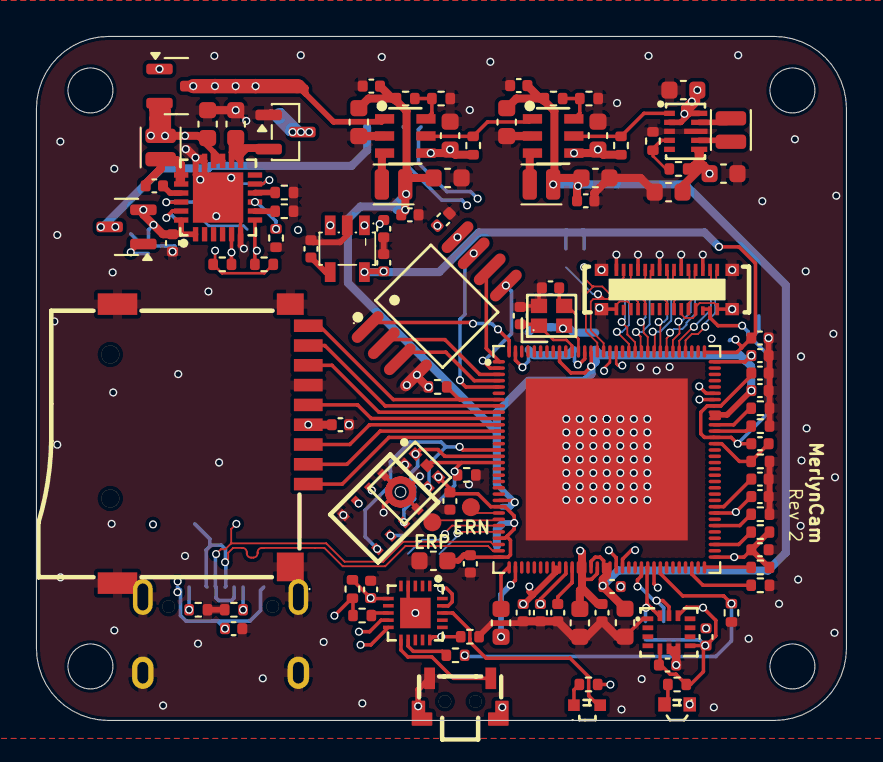
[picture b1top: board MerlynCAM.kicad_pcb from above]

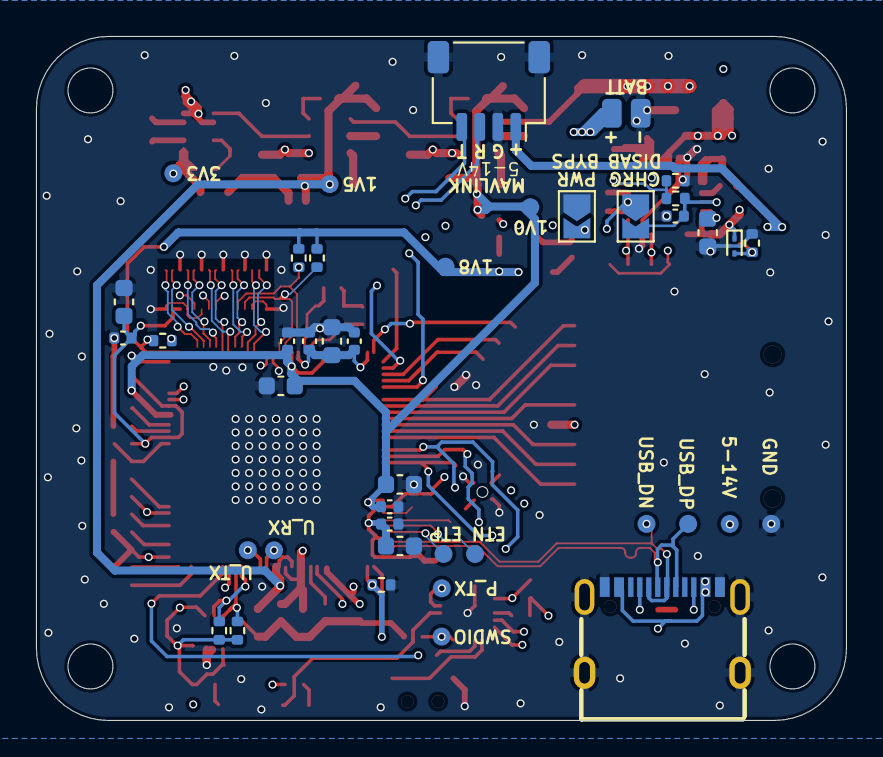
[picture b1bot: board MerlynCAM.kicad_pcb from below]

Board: 4 copper layers, 45.0 x 38.0 mm, 146 parts (42 on the bottom side), 101 nets.

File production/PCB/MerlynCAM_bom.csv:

Designator,Footprint,Quantity,Value,LCSC Part #
BT1,Battery,1,BAT,
"C1, C10, C11, C13, C14, C16, C22, C29, C31, C4, C44, C45, C50, C58, C6, C60, C61, C8",0603,18,10uF,C96446
"C12, C15, C9",0603,3,22uF,C59461
"C17, C21, C23, C24, C26, C28, C3, C30, C32, C33, C34, C35, C36, C37, C38, C39, C40, C41, C42, C43, C46, C47, C48, C49, C51, C52, C53, C54, C55, C56, C57",0402,31,0.1uF,C307331
C18,0402,1,22nF,C1532
"C19, C20, C7",0402,3,1uF,C52923
C2,0402,1,4.7uF,C23733
"C25, C27",0402,2,8pF,C1578
C5,0402,1,47nF,C272875
CN1,CONN-SMD_30P-P0.40_OK-10F030-04-A,1,OK-10F030-04,C9900021743
D1,D_SOD-923,1,Zener,C414245
H1,JST_SH_SM04B-SRSS-TB_1x04-1MP_P1.00mm_Horizontal,1,~,C2845363
"L1, L3, L4",L_Changjiang_FTC201610S,3,1.5uH,C5832343
L2,L_Changjiang_FTC201610S,1,0.47uH,C5832340
LED1,LED-SMD_L1.6-W1.1-RD,1,YLED0602RSIDE,C49446796
LED2,LED-SMD_L1.6-W1.1-R-RD_WHITE,1,WHITE,C46635136
"Q1, Q2, Q3",SOT-23,3,AO3401A,C15127
"R1, R26, R29",0402,3,100k,C25741
R10,0402,1,56k,C25796
"R11, R13, R14, R15, R19, R20, R21, R22, R23, R38, R4, R5, R8, R9",0402,14,10k,C25744
"R12, R16",0402,2,15k,C25756
"R17, R25, R32, R33, R34, R35, R6, R7",0402,8,5.1k,C25905
"R18, R2",0402,2,270R,C2909342
R24,0402,1,36k,C2930004
"R27, R36, R37",0402,3,100R,C25076
R28,0402,1,51k,C25794
R3,0402,1,910R,C2909392
R30,0402,1,4.7k,C25900
R31,0402,1,200k,C25764
SW1,SW-SMD_2P-TS24CA,1,TS24CA,C393942
TP1,TestPoint,1,SWDIO,
TP2,TestPoint,1,USART1_TX,
TP3,TestPoint,1,UART_TX,
TP4,TestPoint,1,UART_RX,
U1,VSON-10_L3.0-W2.0-P0.50-TL,1,TPS63802DLAR,C2845237
U10,SOIC-8_L5.3-W5.3-P1.27-LS8.0-BL,1,W25Q128JVSIQTR,C97521
U11,TF-SMD_TF-115-BCP9,1,TF-115-BCP9,C720505
U12,QFN128_12.3_12.3,1,~,
U2,VQFN-24_L4.0-W4.0-P0.50-TL-EP2.8,1,BQ25606RGER,C374063
"U3, U4",SOT-23-6_L2.9-W1.6-P0.95-LS2.8-BL,2,RT8097CHGE,C3031673
U5,QFN-20_L3.0-W3.0-P0.40-TL-EP1.7,1,CH32V003F4U6,C5299908
U6,SOT-23-5_L3.0-W1.7-P0.95-LS2.8-BR,1,RT9193-18GB,C27416
U7,MIC-SMD_6P-L3.5-W2.7-P0.90-BL,1,ICS43434,C5656610
U8,LGA-14_L3.0-W2.5-P0.50-BR,1,BMI270,C2836813
U9,MIC-SMD_INMP441,1,INMP441,C5438445
USB1,USB-C-SMD_TYPE-C-6PIN-2MD-073,1,TYPE-C 16PIN,C2765186
X1,CRYSTAL-SMD_4P-L2.0-W1.6-BL,1,24MHz,C7303340
